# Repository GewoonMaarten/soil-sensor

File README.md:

# soil-sensor 🌱
Schematic and PCB for a capacitive soil moisture sensor.

**See [latest release](../../releases/latest) for schematic and gerbers.**

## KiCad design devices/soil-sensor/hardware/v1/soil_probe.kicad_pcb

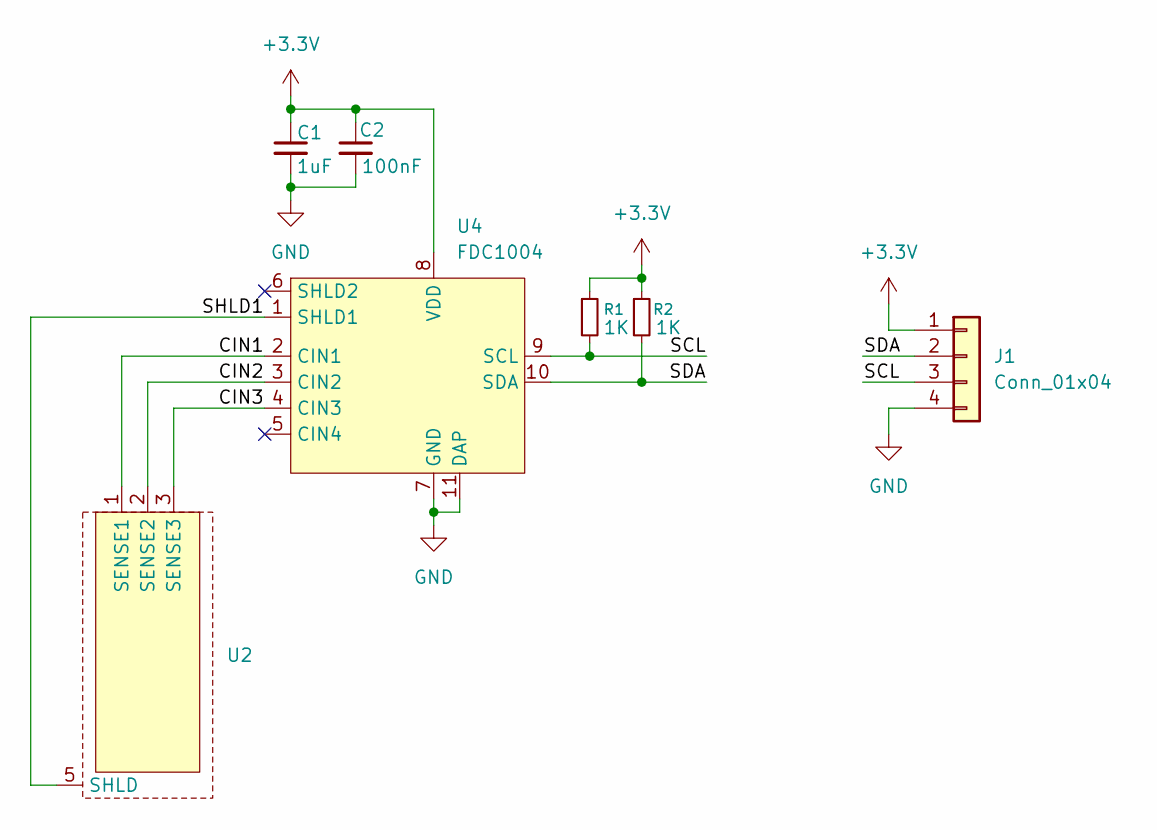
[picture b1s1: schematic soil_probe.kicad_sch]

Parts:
C1: 1uF; C_0603_1608Metric
C2: 100nF; C_0603_1608Metric
J1: Conn_01x04; PinHeader_1x04_P2.54mm_Vertical
R1, R2: 1K; R_0603_1608Metric
U2: SoilPad_03_SHLD
U4: FDC1004; FDC1004DS

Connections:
+3.3V: C1.1, C2.1, J1.1, R1.1, R2.1, U4.8 (VDD)
/CIN1: U2.1 (SENSE1), U4.2 (CIN1)
/CIN2: U2.2 (SENSE2), U4.3 (CIN2)
/CIN3: U2.3 (SENSE3), U4.4 (CIN3)
/SCL: J1.3, R1.2, U4.9 (SCL)
/SDA: J1.2, R2.2, U4.10 (SDA)
/SHLD1: U2.5 (SHLD), U4.1 (SHLD1)
GND: C1.2, C2.2, J1.4, U4.7 (GND), U4.11 (DAP)

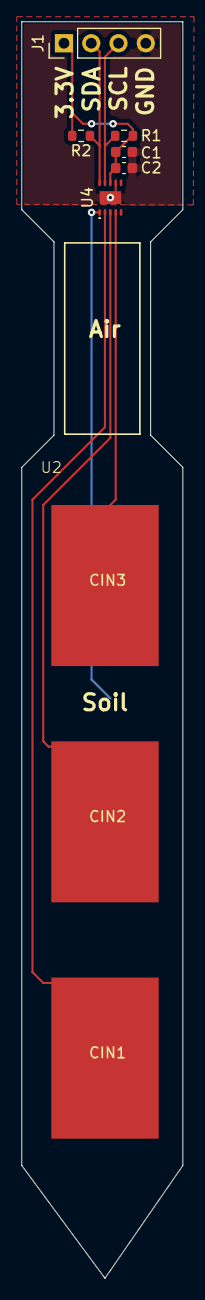
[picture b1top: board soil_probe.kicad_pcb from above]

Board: 2 copper layers, 15.0 x 117.0 mm, 7 parts (0 on the bottom side), 8 nets.

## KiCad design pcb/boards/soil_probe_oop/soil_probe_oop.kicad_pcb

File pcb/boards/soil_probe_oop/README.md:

# Out-of-phase soil sensor

Based on the [Capacitive-Based Liquid Level Sensing Sensor Reference Design](https://www.ti.com/tool/TIDA-00317).

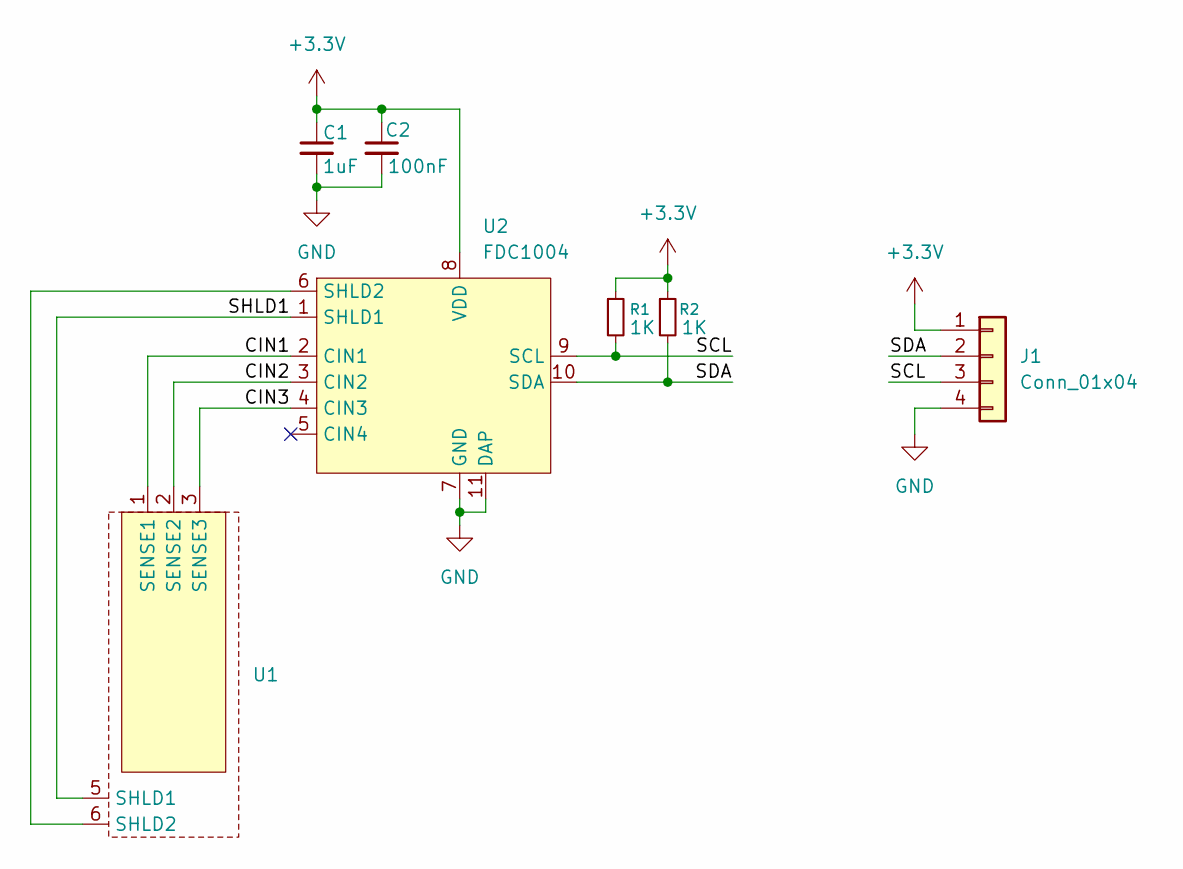
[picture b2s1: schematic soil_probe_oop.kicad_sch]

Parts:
C1: 1uF; C_0603_1608Metric
C2: 100nF; C_0603_1608Metric
J1: Conn_01x04; PinHeader_1x04_P2.54mm_Vertical
R1, R2: 1K; R_0603_1608Metric
U1: SoilPad_OOP
U2: FDC1004; FDC1004DS

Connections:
+3.3V: C1.1, C2.1, J1.1, R1.1, R2.1, U2.8 (VDD)
/CIN1: U1.1 (SENSE1), U2.2 (CIN1)
/CIN2: U1.2 (SENSE2), U2.3 (CIN2)
/CIN3: U1.3 (SENSE3), U2.4 (CIN3)
/SCL: J1.3, R1.2, U2.9 (SCL)
/SDA: J1.2, R2.2, U2.10 (SDA)
/SHLD1: U1.5 (SHLD1), U2.1 (SHLD1)
GND: C1.2, C2.2, J1.4, U2.7 (GND), U2.11 (DAP)
unnamed: U1.6 (SHLD2), U2.6 (SHLD2)

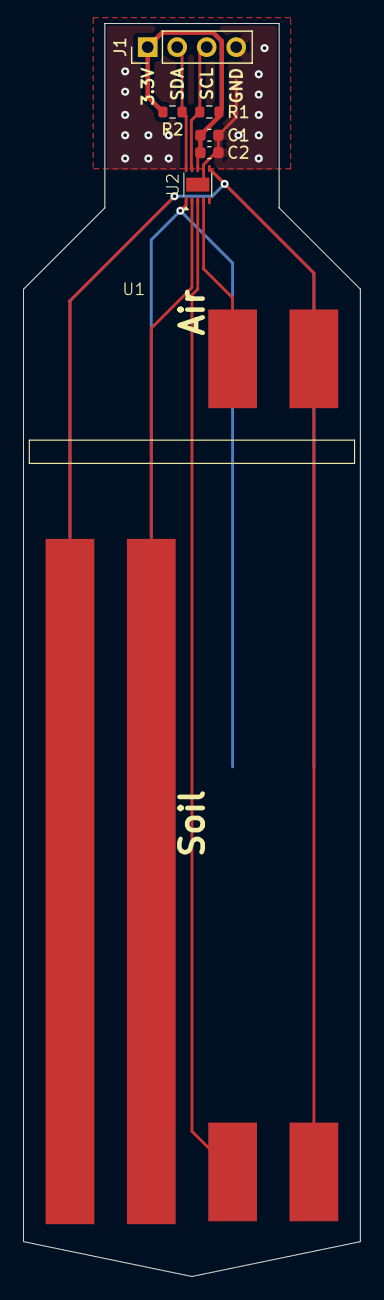
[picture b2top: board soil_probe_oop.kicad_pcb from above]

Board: 2 copper layers, 29.0 x 107.9 mm, 7 parts (0 on the bottom side), 9 nets.

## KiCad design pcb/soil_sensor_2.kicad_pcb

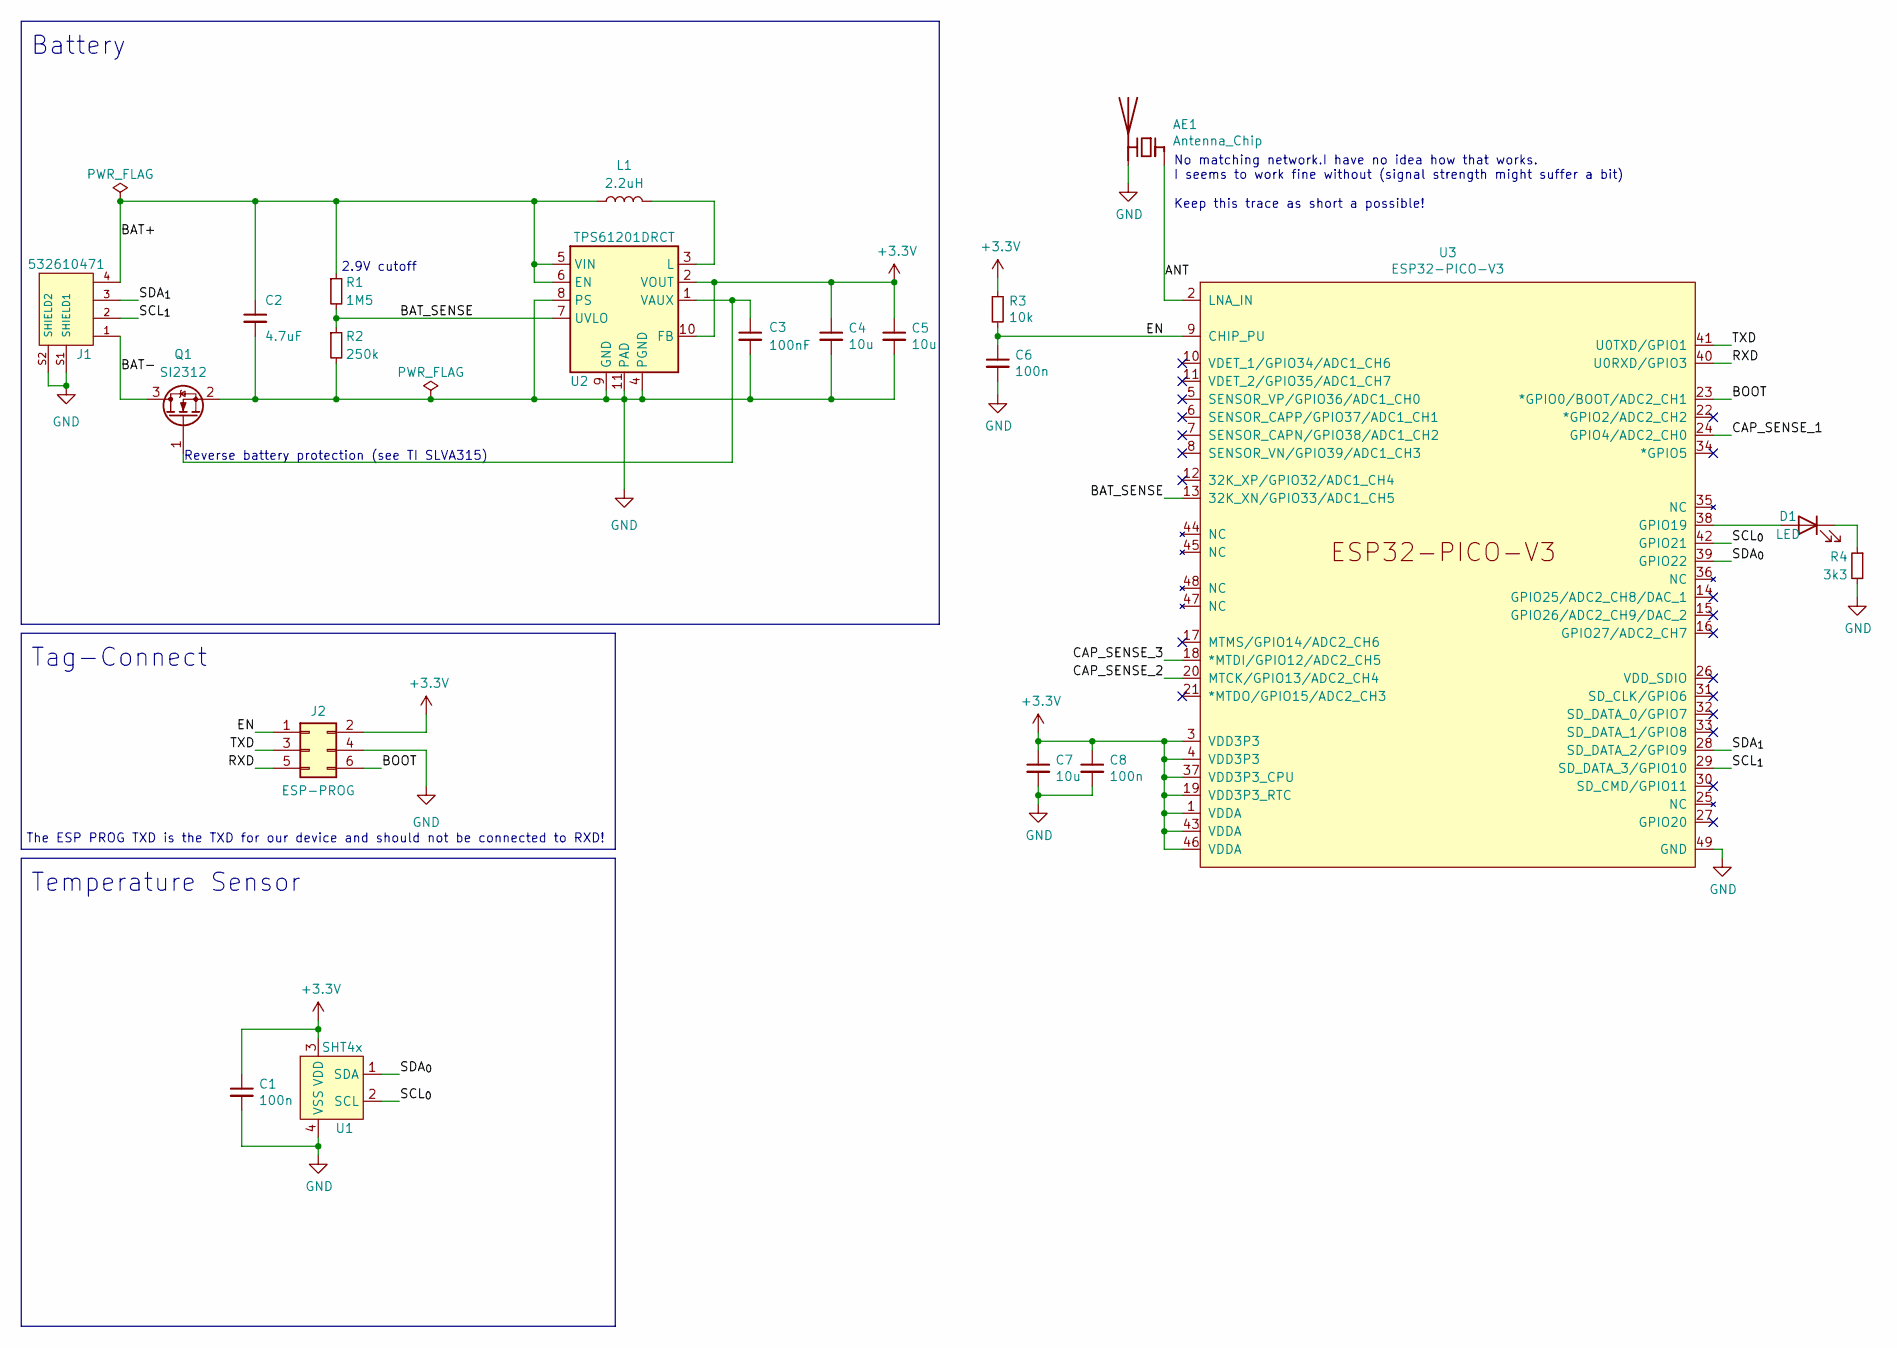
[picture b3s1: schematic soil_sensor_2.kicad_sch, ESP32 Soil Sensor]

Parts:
AE1: Antenna_Chip; Texas_SWRA117D_2.4GHz_Right
C1, C6, C8: 100n; C_0603_1608Metric
C2: 4.7uF; C_0603_1608Metric
C3: 100nF; C_0603_1608Metric
C4, C5, C7: 10u; C_0805_2012Metric
D1: LED; LED_0603_1608Metric
J1: 532610471; MOLEX_532610471; PARTREV J
J2: ESP-PROG; Tag-Connect_TC2030-IDC-NL_2x03_P1.27mm_Vertical
L1: 2.2uH; L_Taiyo-Yuden_NR-40xx; Digikey NRS4018T2R2MDGJ
Q1: SI2312; SOT-23; Digikey SI2312BDS-T1-E3CT-ND
R1: 1M5; R_0603_1608Metric; Digikey 541-2.87MHCT-ND
R2: 250k; R_0603_1608Metric
R3: 10k; R_0603_1608Metric
R4: 3k3; R_0603_1608Metric
U1: SHT4x; XDCR_SHT40-AD1B-R2
U2: TPS61201DRCT; Texas_S-PVSON-N10_ThermalVias; Digikey 296-21684-1-ND
U3: ESP32-PICO-V3; QFN-48-1EP_7x7mm_P0.5mm_EP5.15x5.15mm; Digikey 1965-ESP32-PICO-V3CT-ND

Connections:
+3V3: C1.1, C4.1, C5.1, C7.1, C8.1, J2.2, R3.1, U1.3 (VDD), U2.2 (VOUT), U2.10 (FB), U3.1 (VDDA), U3.3 (VDD3P3), U3.4 (VDD3P3), U3.19 (VDD3P3_RTC), U3.37 (VDD3P3_CPU), U3.43 (VDDA), U3.46 (VDDA)
/ANT: AE1.1 (FEED), U3.2 (LNA_IN)
/BAT+: C2.1, J1.4, L1.1, R1.1, U2.5 (VIN), U2.6 (EN)
/BAT-: J1.1, Q1.3 (D)
/BAT_SENSE: R1.2, R2.1, U2.7 (UVLO), U3.13 (32K_XN/GPIO33/ADC1_CH5)
/BOOT: J2.6, U3.23 (*GPIO0/BOOT/ADC2_CH1)
/CAP_SENSE_1: U3.24 (GPIO4/ADC2_CH0)
/CAP_SENSE_2: U3.20 (MTCK/GPIO13/ADC2_CH4)
/CAP_SENSE_3: U3.18 (*MTDI/GPIO12/ADC2_CH5)
/EN: C6.1, J2.1, R3.2, U3.9 (CHIP_PU)
/RXD: J2.5, U3.40 (U0RXD/GPIO3)
/SCL_{0}: U1.2 (SCL), U3.42 (GPIO21)
/SCL_{1}: J1.2, U3.29 (SD_DATA_3/GPIO10)
/SDA_{0}: U1.1 (SDA), U3.39 (GPIO22)
/SDA_{1}: J1.3, U3.28 (SD_DATA_2/GPIO9)
/TXD: J2.3, U3.41 (U0TXD/GPIO1)
GND: AE1.2 (PCB_Trace), C1.2, C2.2, C3.2, C4.2, C5.2, C6.2, C7.2, C8.2, J1.S1 (SHIELD1), J1.S2 (SHIELD2), J2.4, Q1.2 (S), R2.2, R4.2, U1.4 (VSS), U2.4 (PGND), U2.8 (PS), U2.9 (GND), U2.11 (PAD), U3.49 (GND)
unnamed: C3.1, Q1.1 (G), U2.1 (VAUX)
unnamed: D1.1 (K), R4.1
unnamed: D1.2 (A), U3.38 (GPIO19)
unnamed: L1.2, U2.3 (L)

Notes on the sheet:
Temperature Sensor
The ESP PROG TXD is the TXD for our device and should not be connected to RXD!
Tag-Connect
Battery
Reverse battery protection (see TI SLVA315)
2.9V cutoff
No matching network.I have no idea how that works. I seems to work fine without (signal strength might suffer a bit) Keep this trace as short a possible!

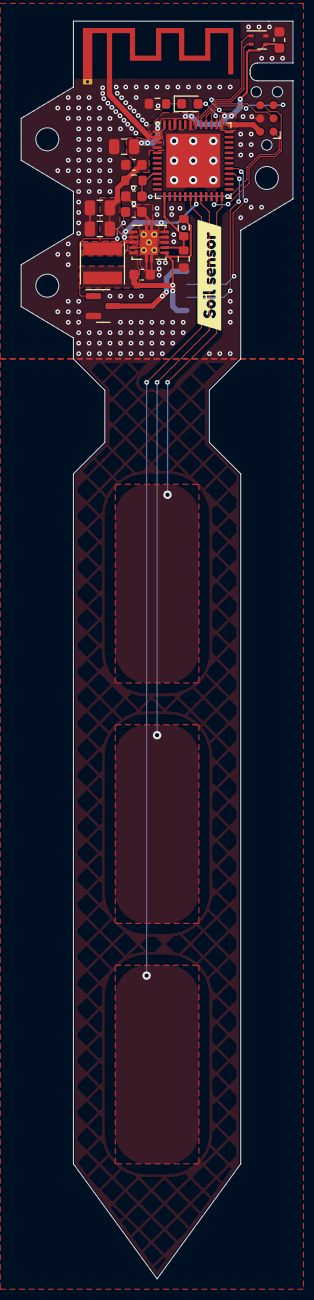
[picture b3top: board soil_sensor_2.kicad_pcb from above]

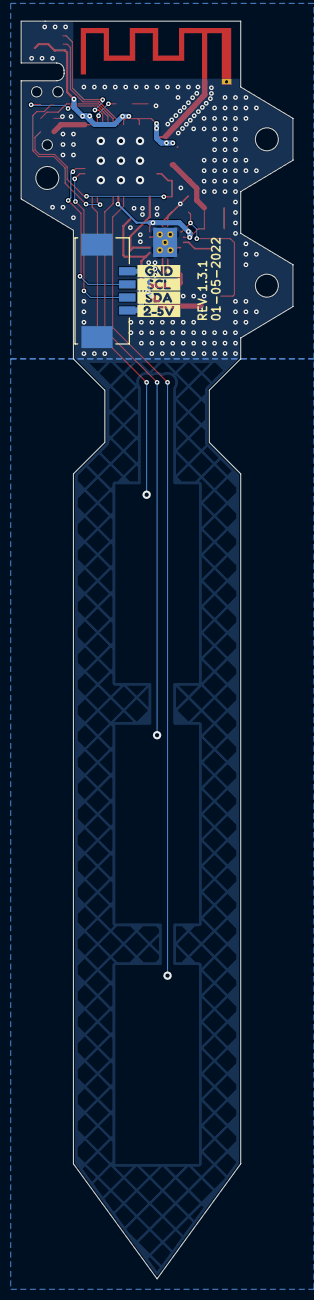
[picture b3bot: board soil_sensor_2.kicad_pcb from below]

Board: 2 copper layers, 26.0 x 120.3 mm, 26 parts (5 on the bottom side), 18 nets.

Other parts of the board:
kibuzzard-61BE000A: G***; kibuzzard-61BE000A
kibuzzard-61BE001F: G***; kibuzzard-61BE001F
kibuzzard-61BE0016: G***; kibuzzard-61BE0016
kibuzzard-61BE0025: G***; kibuzzard-61BE0025
kibuzzard-61BE0345: G***; kibuzzard-61BE0345

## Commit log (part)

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2018-11-24 Added first code
2021-11-27 update BMS
    now using the TPS61201DRCT
2021-11-27 added some comments
2021-11-27 add readme
2021-11-27 update kicad version
2021-11-27 update board version label
2022-04-29 move battery off pcb
2022-04-29 chore: move pcb files in new directory
2022-04-29 chore: add development container
2022-04-30 fix: add locales to docker container
    This makes idf.py menuconfig work
2022-04-30 chore: run docker container privileged
    Easier to use when working with serial devices
2022-04-30 chore: add cpp extension pack properties
2022-04-30 chore: add soil sensor source code
2022-05-01 chore: add cutout to improve temperature isolation
2022-05-26 chore: add bme68x and bsec libraries
2023-02-20 chore: add bme68x and bsec library
2023-02-20 chore: move gitignore
2023-02-20 chore: add serial ports to dev container
2023-02-20 chore: add wifi component
2023-02-20 feat: add ble central hub
2023-02-20 chore: remove unused function
2023-02-22 chore: add mqtt discovery payload builder
2023-03-08 chore: cleanup mqtt_discovery_sensor
